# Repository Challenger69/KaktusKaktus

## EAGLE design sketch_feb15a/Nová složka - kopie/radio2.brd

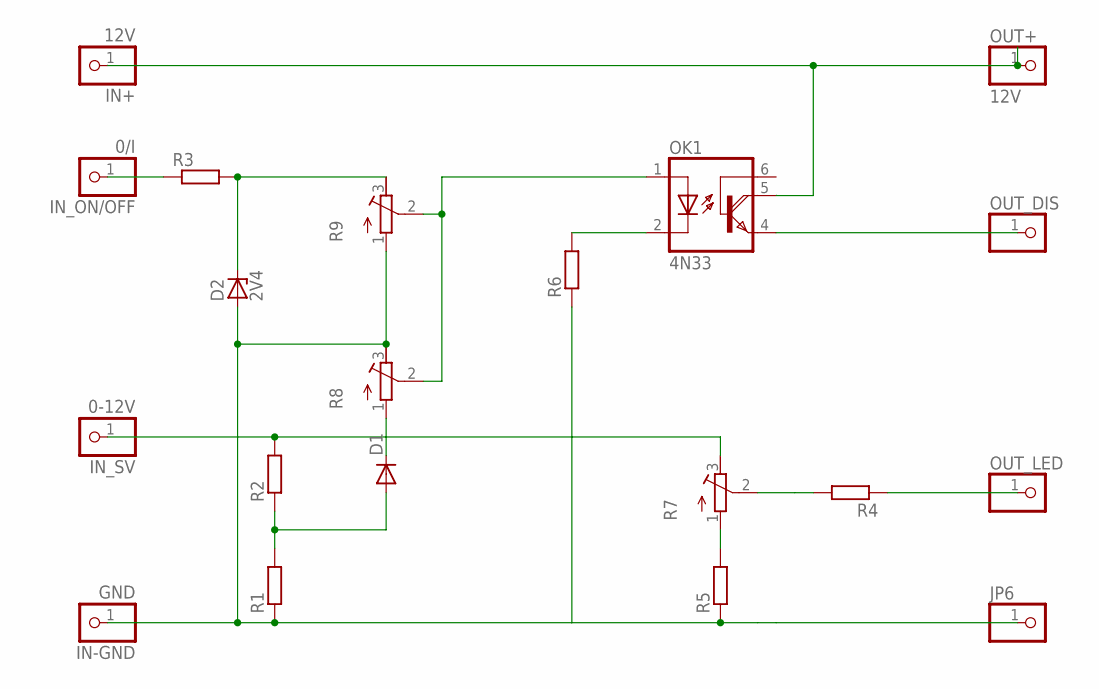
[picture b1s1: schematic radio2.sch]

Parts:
D1: 1N4004; DO41-10
D2: 2V4; DO35Z10
IN+: 12V; 1X01
IN-GND: GND; 1X01
IN_ON/OFF: 0/I; 1X01
IN_SV: 0-12V; 1X01
JP6: PINHD-1X1; 1X01
OK1: 4N33; DIL06
OUT+: 12V; 1X01
OUT_DIS: PINHD-1X1; 1X01
OUT_LED: PINHD-1X1; 1X01
R1, R2, R3, R4, R5, R6: R-EU_0207/7; 0207/7
R7, R8, R9: R-TRIMM3339P; RTRIM3339P

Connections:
unnamed: D2.A, IN-GND.1, JP6.1, R1.1, R5.1, R6.1, R8.3 (E), R9.1 (A)
unnamed: D1.A, R1.2, R2.1
unnamed: IN_SV.1, R2.2, R7.3 (E)
unnamed: IN_ON/OFF.1, R3.1
unnamed: OK1.2 (C), R6.2
unnamed: R5.2, R7.1 (A)
unnamed: R4.2, R7.2 (S)
unnamed: IN+.1, OK1.5 (COL), OUT+.1
unnamed: OUT_LED.1, R4.1
unnamed: OK1.4 (E), OUT_DIS.1
unnamed: D1.C, R8.1 (A)
unnamed: D2.C, R3.2, R9.3 (E)
unnamed: OK1.1 (A), R8.2 (S), R9.2 (S)

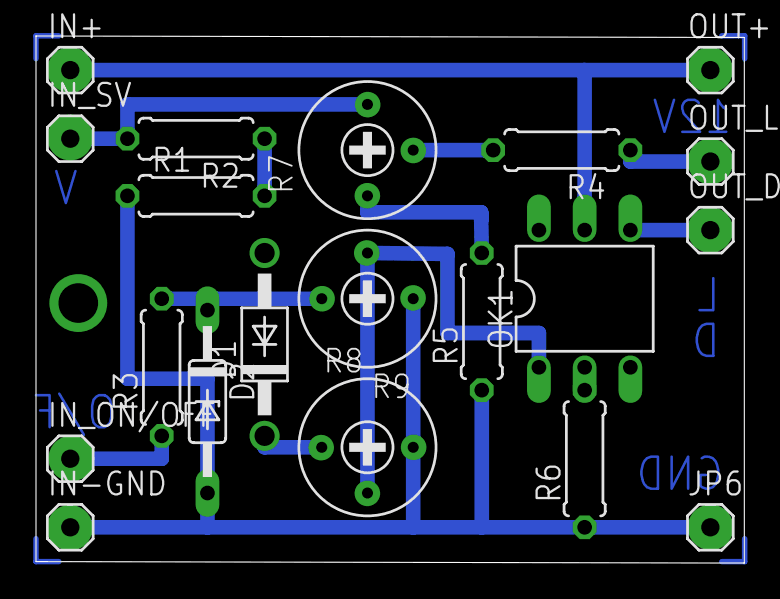
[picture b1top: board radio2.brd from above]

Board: 2 copper layers, 39.4 x 29.3 mm, 20 parts (0 on the bottom side), 13 nets.

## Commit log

2023-05-11 Matice
2023-05-13 Create Mat. display
